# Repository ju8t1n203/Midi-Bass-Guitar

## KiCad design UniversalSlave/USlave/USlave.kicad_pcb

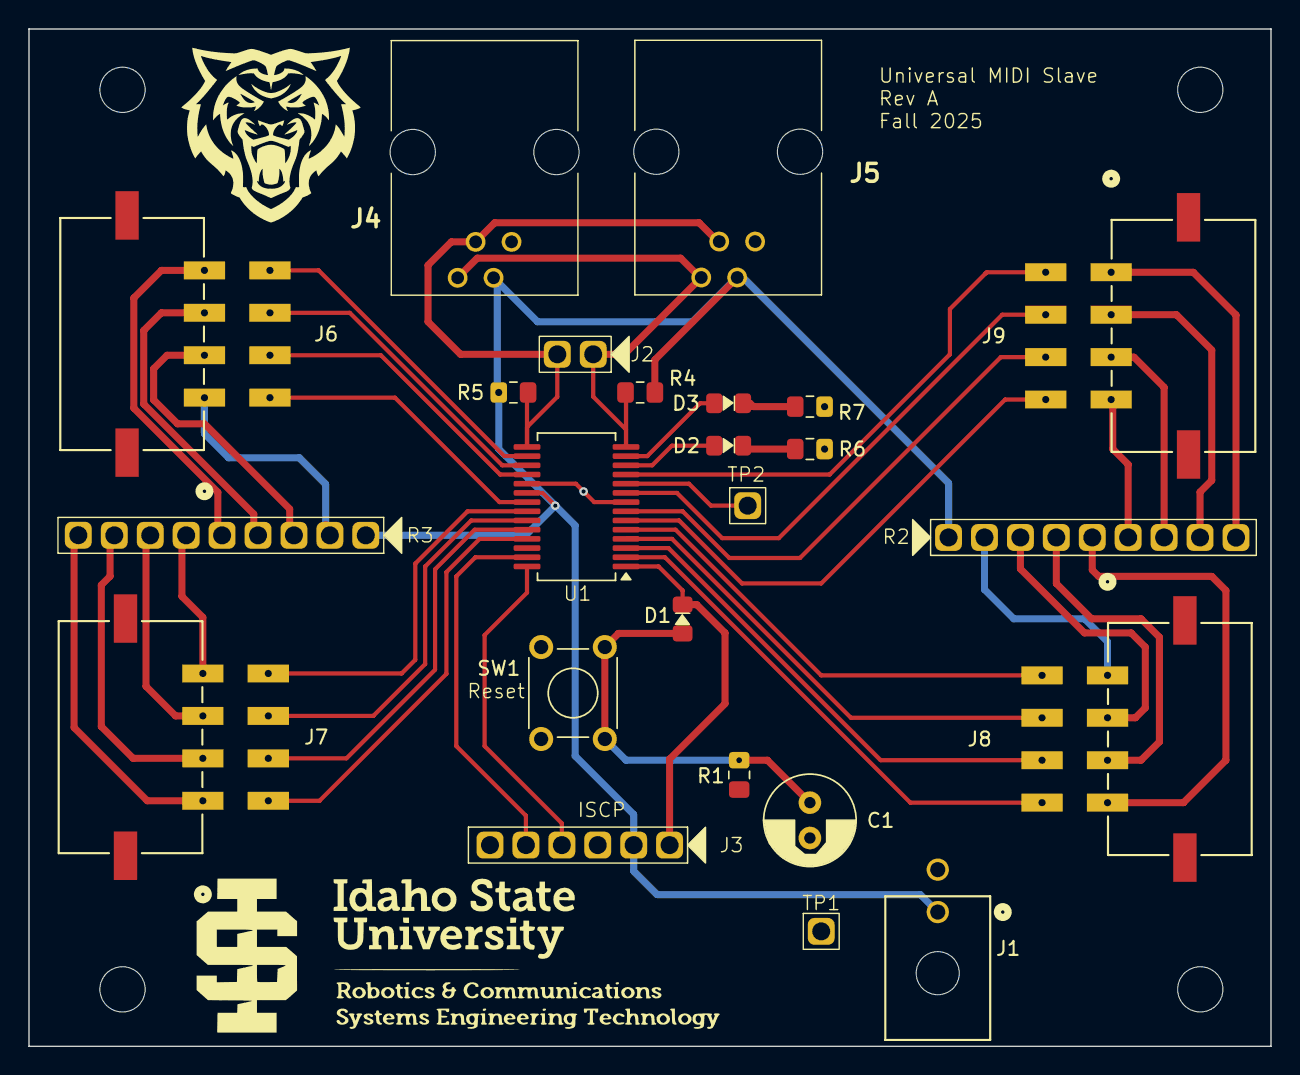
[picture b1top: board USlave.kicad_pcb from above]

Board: 2 copper layers, 87.8 x 71.9 mm, 24 parts (0 on the bottom side), 45 nets.

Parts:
C1: 10µF; C_Radial_D6.3mm_H11.0mm_P2.50mm
D1: 1N4148; D_0805
D2: Powered; D_0805
D3: Status; D_0805
J1: Power In; 2PinMolex
J2: I2C Test Point; 1X2_100mil_Header
J3: ISCP; 1X6_100mil_Header
J4: I2C Through; RJ11
J5: I2C In; RJ11
J6: 0-3; 8PinMolex_3.00mmPitch
J7: 4-7; 8PinMolex_3.00mmPitch
J8: 8-11; 8PinMolex_3.00mmPitch
J9: 12-15; 8PinMolex_3.00mmPitch
R1: 10KΩ; C_0805
R2, R3: 330Ω; 1x9_100mil_Header
R4, R5: 2.2KΩ; C_0805
R6, R7: 330Ω; C_0805
SW1: Reset; SW_TH_Tactile_Omron_B3F-100x
TP1: GND; 1X1_100mil_Header
TP2: Clock Out; 1X1_100mil_Header
U1: PIC16F1788; SSOP-28_5.3x10.2mm_P0.65mm

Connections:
GND: C1.2, J1.2, J3.3, J4.1, J5.1, R6.2, R7.2, SW1.1, TP1.1, U1.8 (V_{SS}), U1.19 (V_{SS})
unnamed: C1.1, D1.2 (A), R1.2, SW1.2
unnamed: D1.1 (K), J3.1, U1.1 (RE3/~MCLR/V_{PP})
unnamed: D2.2 (A), U1.12 (RC1)
unnamed: D2.1 (K), R6.1
unnamed: D3.2 (A), U1.13 (RC2)
unnamed: D3.1 (K), R7.1
unnamed: J8.1, R2.2 (R1)
unnamed: J8.2, R2.3 (R2)
unnamed: J8.3, R2.4 (R3)
unnamed: J8.4, R2.5 (R4)
unnamed: J9.4, R2.6 (R5)
unnamed: J9.3, R2.7 (R6)
unnamed: J9.2, R2.8 (R7)
unnamed: J9.1, R2.9 (R8)
unnamed: J6.1, R3.2 (R1)
unnamed: J6.2, R3.3 (R2)
unnamed: J6.3, R3.4 (R3)
unnamed: J6.4, R3.5 (R4)
unnamed: J7.4, R3.6 (R5)
unnamed: J7.3, R3.7 (R6)
unnamed: J7.2, R3.8 (R7)
unnamed: J7.1, R3.9 (R8)
unnamed: J3.5, U1.27 (ICSPCLK/RB6)
unnamed: J3.4, U1.28 (ICSPDAT/RB7)
unnamed: J8.8, U1.2 (RA0)
unnamed: J8.7, U1.3 (RA1)
unnamed: J8.6, U1.4 (RA2)
unnamed: J8.5, U1.5 (RA3)
unnamed: J9.8, U1.6 (RA4)
unnamed: J9.7, U1.7 (RA5)
unnamed: TP2.1, U1.10 (RA6)
unnamed: J9.6, U1.9 (RA7)
unnamed: J6.5, U1.21 (RB0)
unnamed: J7.8, U1.22 (RB1)
unnamed: J7.7, U1.23 (RB2)
unnamed: J7.6, U1.24 (RB3)
unnamed: J7.5, U1.25 (RB4)
unnamed: J9.5, U1.11 (RC0)
unnamed: J2.1, J4.4, J5.4, R4.2, U1.14 (RC3)
unnamed: J2.2, J4.3, J5.3, R5.2, U1.15 (RC4)
unnamed: J6.8, U1.16 (RC5)
unnamed: J6.7, U1.17 (RC6)
unnamed: J6.6, U1.18 (RC7)
unnamed: J1.1, J3.2, J4.2, J5.2, R2.1 (COM), R3.1 (COM), R4.1, R5.1, U1.20 (V_{DD})

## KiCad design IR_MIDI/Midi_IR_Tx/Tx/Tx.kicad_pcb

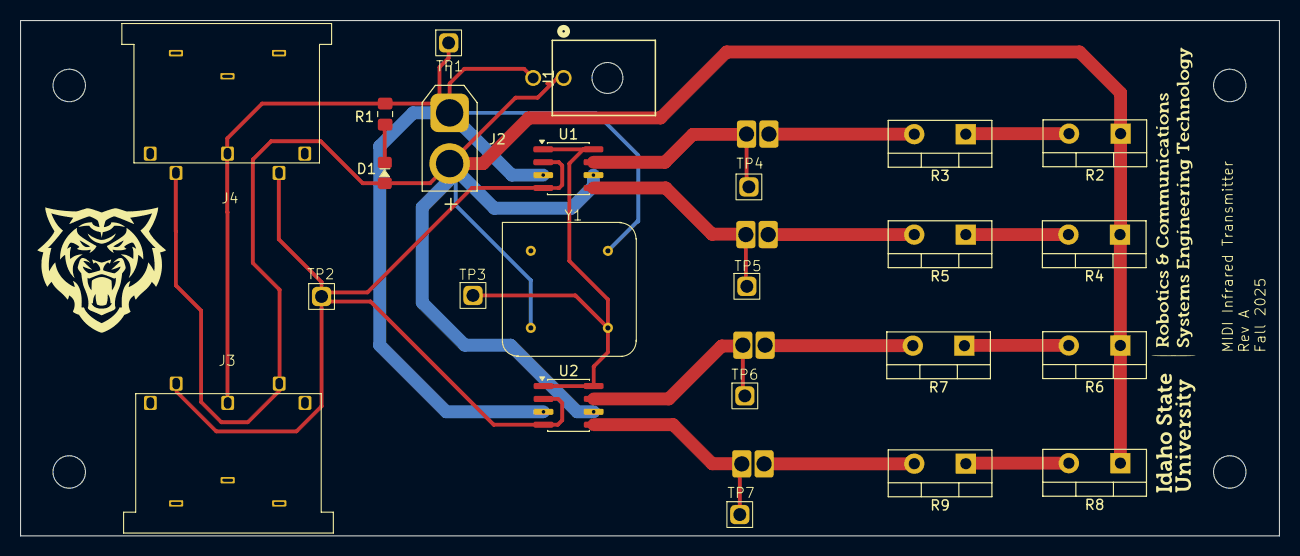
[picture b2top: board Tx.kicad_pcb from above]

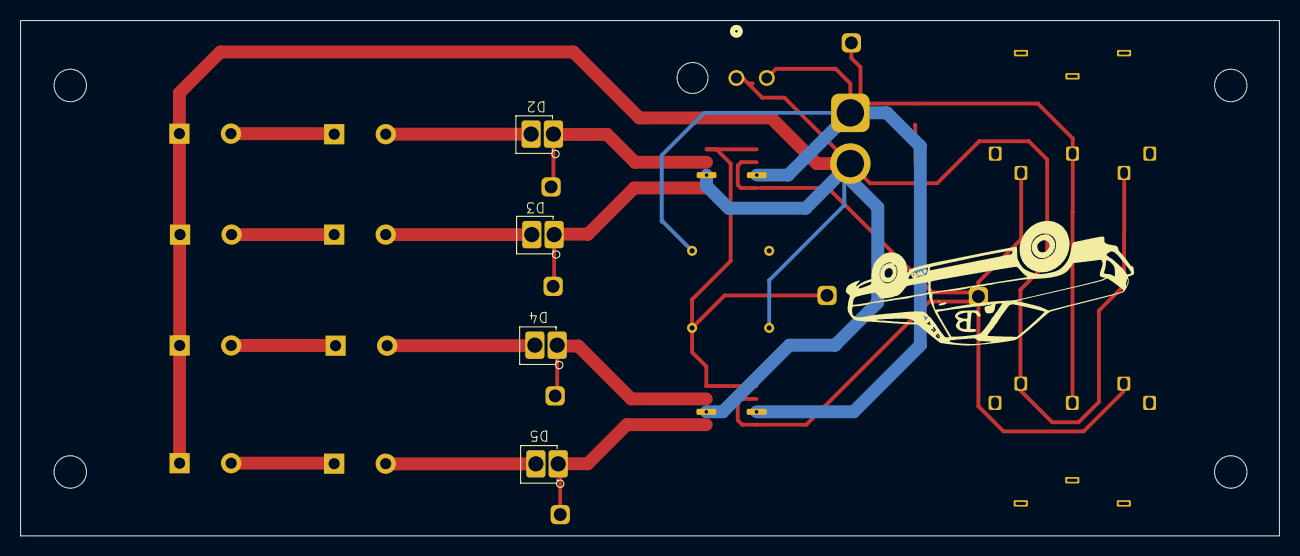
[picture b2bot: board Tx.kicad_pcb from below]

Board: 2 copper layers, 124.1 x 50.8 mm, 28 parts (4 on the bottom side), 17 nets.

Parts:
D1: LED_Filled; D_0805
D2, D3, D4, D5: D_Filled; Fat_2Pin_D
J1: FanPower; 2PinMolex
J2: Power In; AMASS_XT30U-F_1x02_P5.0mm_Vertical
J3: MIDI Thr; DIN-5PIN_MIDI
J4: MIDI in; DIN-5PIN_MIDI
R1: 330Ω; C_0805
R2, R3, R4, R5, R6, R7, R8, R9: 2Ω; TO-220-2_Vertical
TP1: GND; 1X1_100mil_Header
TP2: MIDI_Input; 1X1_100mil_Header
TP3: 1MHzTP; 1X1_100mil_Header
TP4: IR1; 1X1_100mil_Header
TP5: IR2; 1X1_100mil_Header
TP6: IR3; 1X1_100mil_Header
TP7: IR4; 1X1_100mil_Header
U1, U2: MCP14E3; SOIC-8_3.9x4.9mm_P1.27mm
Y1: 1MHz; 300x300Mil_4Pin_Y

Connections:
GND: J1.2, J2.1, J3.2, J4.2, R1.2, TP1.1, U1.3 (GND), U2.3 (GND), Y1.4
unnamed: D1.1 (K), R1.1
unnamed: D2.1 (A), R3.2
unnamed: D2.2 (K), TP4.1, U1.7 (~OUTA)
unnamed: D3.1 (A), R5.2
unnamed: D3.2 (K), TP5.1, U1.5 (~OUTB)
unnamed: D4.1 (A), R7.2
unnamed: D4.2 (K), TP6.1, U2.7 (~OUTA)
unnamed: D5.1 (A), R9.2
unnamed: D5.2 (K), TP7.1, U2.5 (~OUTB)
unnamed: R2.2, R3.1
unnamed: R4.2, R5.1
unnamed: R6.2, R7.1
unnamed: R8.2, R9.1
unnamed: TP3.1, U1.1 (ENA), U1.8 (ENB), U2.1 (ENA), U2.8 (ENB), Y1.5
unnamed: J3.5, J4.5, TP2.1, U1.2 (INA), U1.4 (INB), U2.2 (INA), U2.4 (INB)
unnamed: D1.2 (A), J1.1, J2.2, J3.4, J4.4, R2.1, R4.1, R6.1, R8.1, U1.6 (VCC), U2.6 (VCC), Y1.8

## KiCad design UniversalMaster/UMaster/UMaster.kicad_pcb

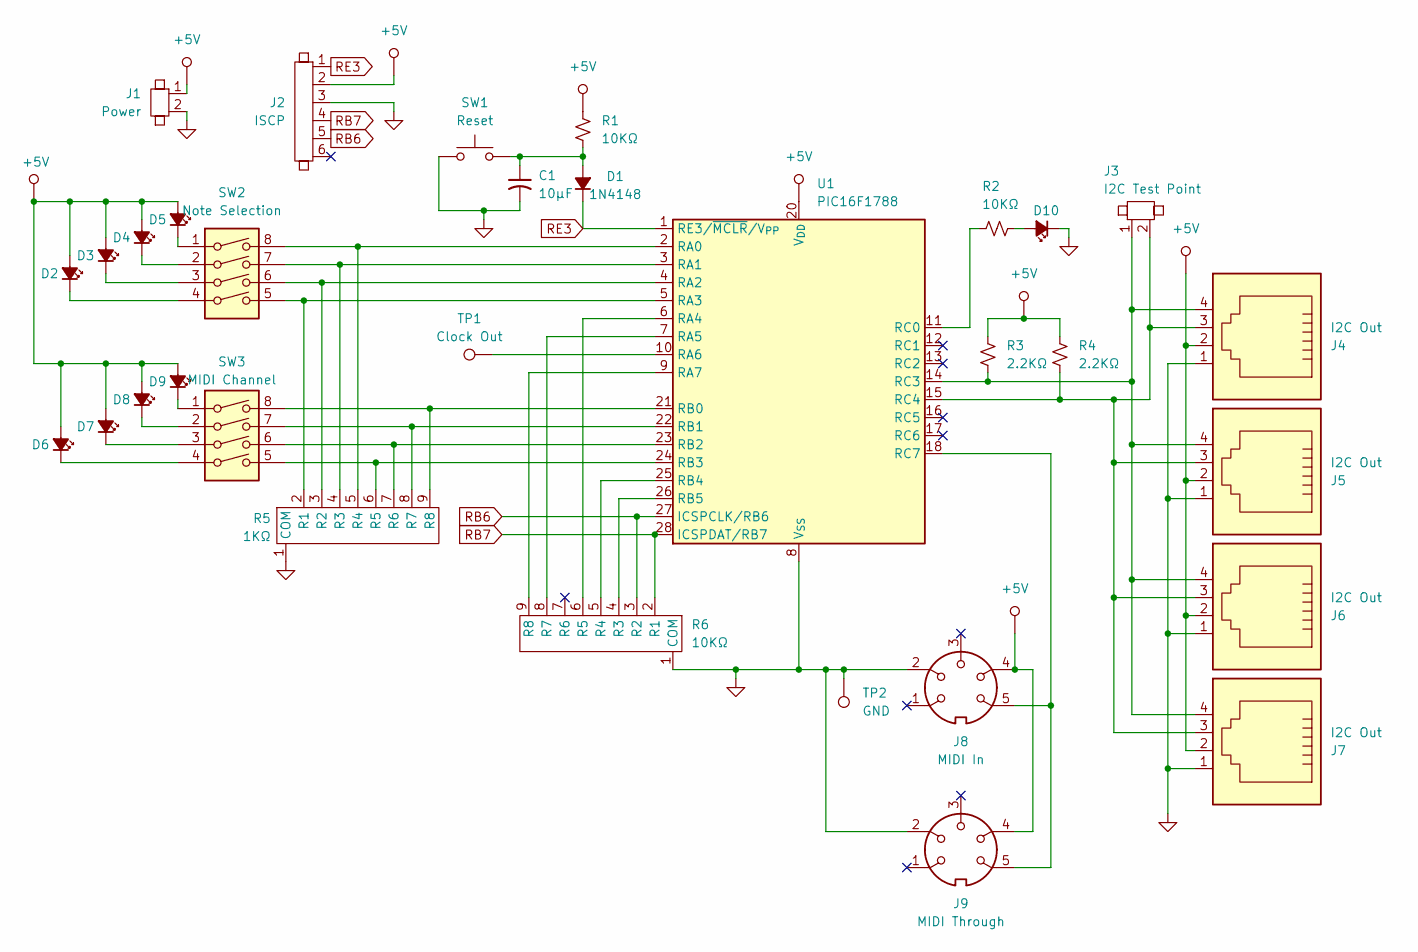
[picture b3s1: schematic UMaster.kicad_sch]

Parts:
C1: 10µF; C_Radial_D6.3mm_H11.0mm_P2.50mm
D1: 1N4148; D_0805
D2, D3, D4, D5, D6, D7, D8, D9, D10: LED_Small_Filled; D_0805
J1: Power; 2PinMolex
J2: ISCP; 1X6_100mil_Header
J3: I2C Test Point; 1X2_100mil_Header
J4, J5, J6, J7: I2C Out; RJ11
J8: MIDI In; DIN-5PIN_MIDI
J9: MIDI Through; DIN-5PIN_MIDI
R1, R2: 10KΩ; C_0805
R3, R4: 2.2KΩ; C_0805
R5: 1KΩ; 1x9_100mil_Header
R6: 10KΩ; 1x9_100mil_Header
SW1: Reset; SW_PUSH_6mm
SW2: Note Selection; DIP-8_W7.62mm
SW3: MIDI Channel; DIP-8_W7.62mm
TP1: Clock Out; 1X1_100mil_Header
TP2: GND; 1X1_100mil_Header
U1: PIC16F1788; QFN-28-1EP_6x6mm_P0.65mm_EP4.25x4.25mm

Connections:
GND: C1.2, D10.1 (K), J1.2, J2.3, J4.1, J5.1, J6.1, J7.1, J8.2, J9.2, R5.1 (COM), R6.1 (COM), SW1.1, TP2.1, U1.8 (V_{SS}), U1.19 (V_{SS})
unnamed: C1.1, D1.2 (A), R1.2, SW1.2
unnamed: D2.1 (K), SW2.4
unnamed: D3.1 (K), SW2.3
unnamed: D4.1 (K), SW2.2
unnamed: D5.1 (K), SW2.1
unnamed: D6.1 (K), SW3.4
unnamed: D7.1 (K), SW3.3
unnamed: D8.1 (K), SW3.2
unnamed: D9.1 (K), SW3.1
unnamed: D10.2 (A), R2.2
unnamed: R5.2 (R1), SW2.5, U1.5 (RA3)
unnamed: R5.3 (R2), SW2.6, U1.4 (RA2)
unnamed: R5.4 (R3), SW2.7, U1.3 (RA1)
unnamed: R5.5 (R4), SW2.8, U1.2 (RA0)
unnamed: R5.6 (R5), SW3.5, U1.24 (RB3)
unnamed: R5.7 (R6), SW3.6, U1.23 (RB2)
unnamed: R5.8 (R7), SW3.7, U1.22 (RB1)
unnamed: R5.9 (R8), SW3.8, U1.21 (RB0)
unnamed: R6.4 (R3), U1.26 (RB5)
unnamed: R6.5 (R4), U1.25 (RB4)
unnamed: R6.6 (R5), U1.6 (RA4)
unnamed: R6.8 (R7), U1.7 (RA5)
unnamed: R6.9 (R8), U1.9 (RA7)
unnamed: TP1.1, U1.10 (RA6)
unnamed: R2.1, U1.11 (RC0)
unnamed: J3.1, J4.4, J5.4, J6.4, J7.4, R3.2, U1.14 (RC3)
unnamed: J3.2, J4.3, J5.3, J6.3, J7.3, R4.2, U1.15 (RC4)
unnamed: J8.5, J9.5, U1.18 (RC7)
RB6: J2.5, R6.3 (R2), U1.27 (ICSPCLK/RB6)
RB7: J2.4, R6.2 (R1), U1.28 (ICSPDAT/RB7)
RE3: D1.1 (K), J2.1, U1.1 (RE3/~MCLR/V_{PP})

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
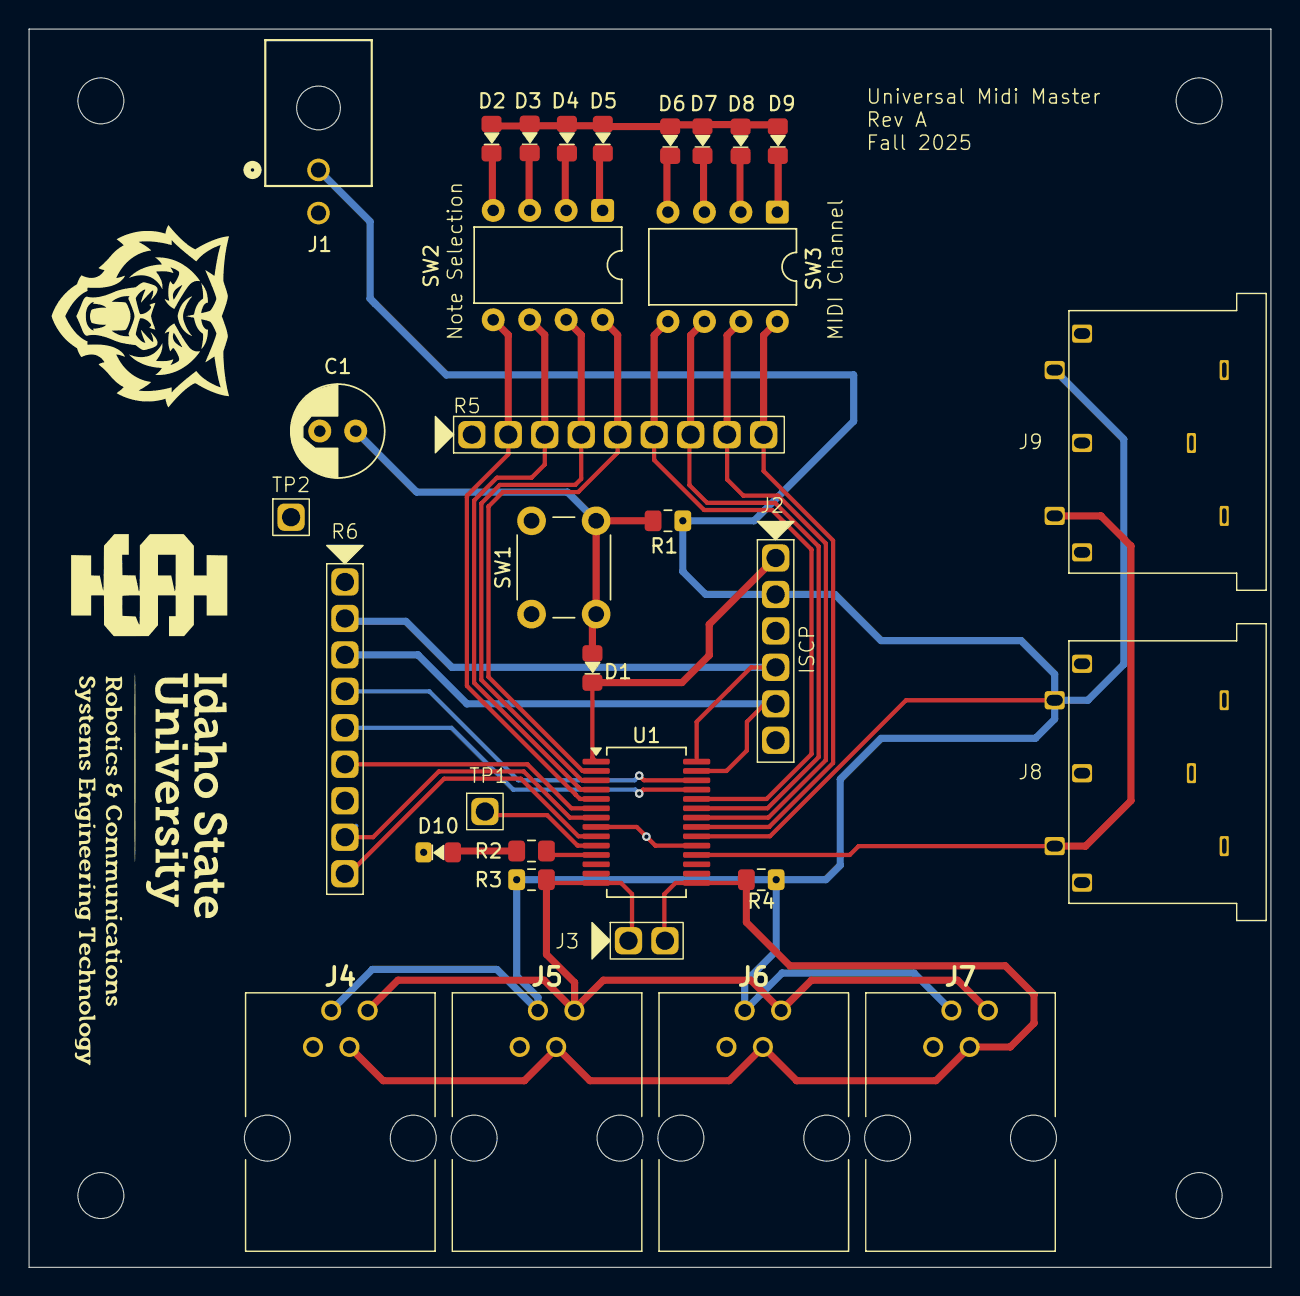
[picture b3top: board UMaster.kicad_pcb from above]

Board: 2 copper layers, 86.5 x 86.2 mm, 32 parts (0 on the bottom side), 34 nets.

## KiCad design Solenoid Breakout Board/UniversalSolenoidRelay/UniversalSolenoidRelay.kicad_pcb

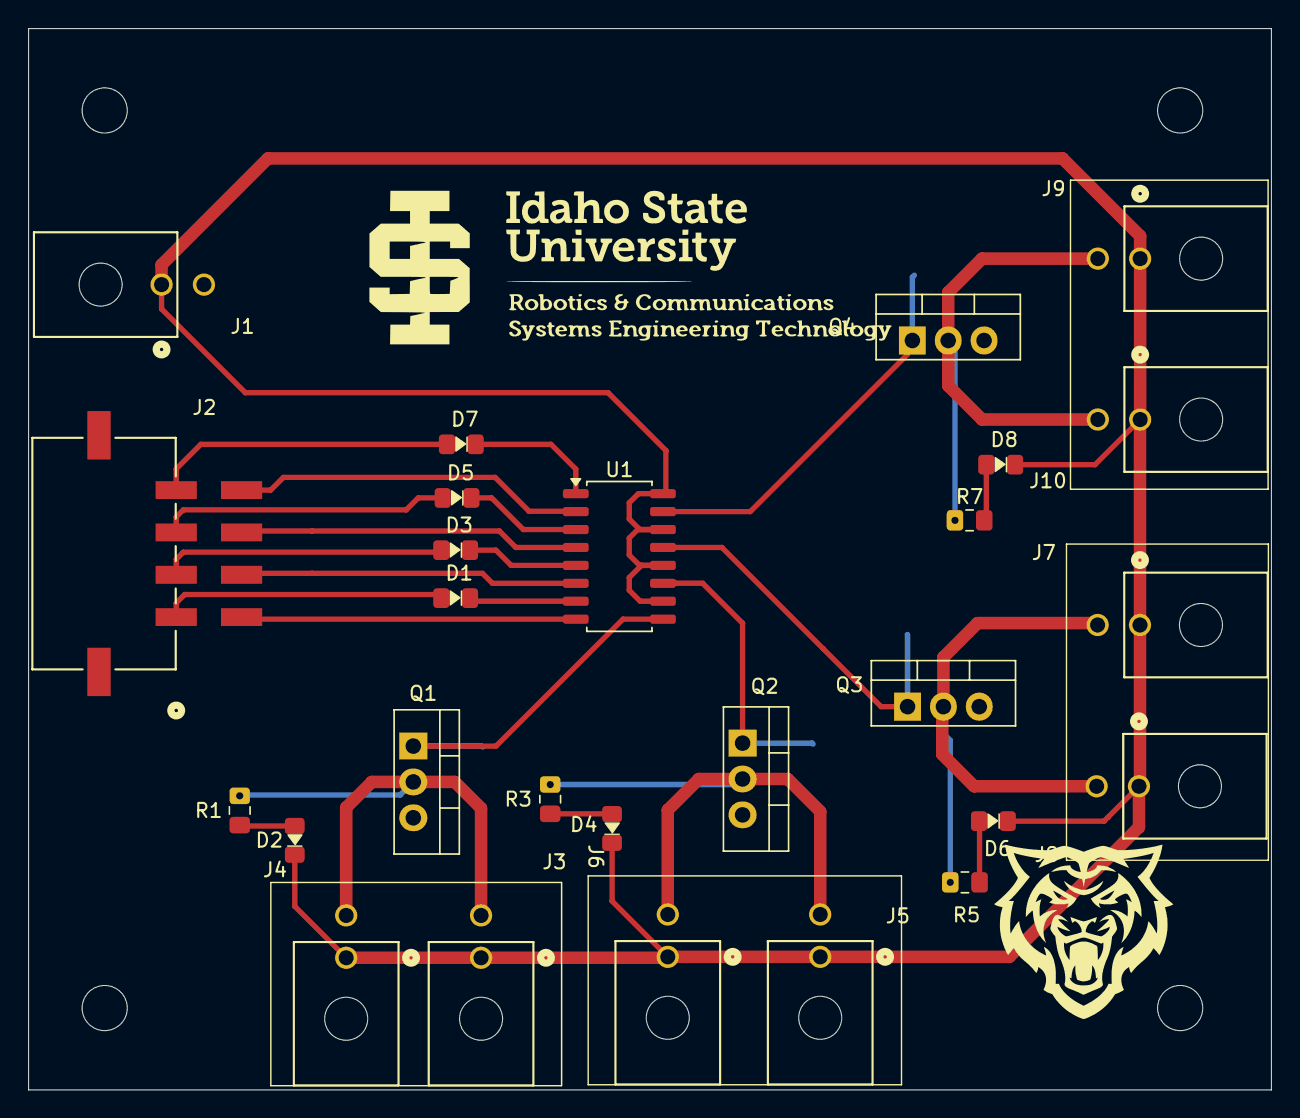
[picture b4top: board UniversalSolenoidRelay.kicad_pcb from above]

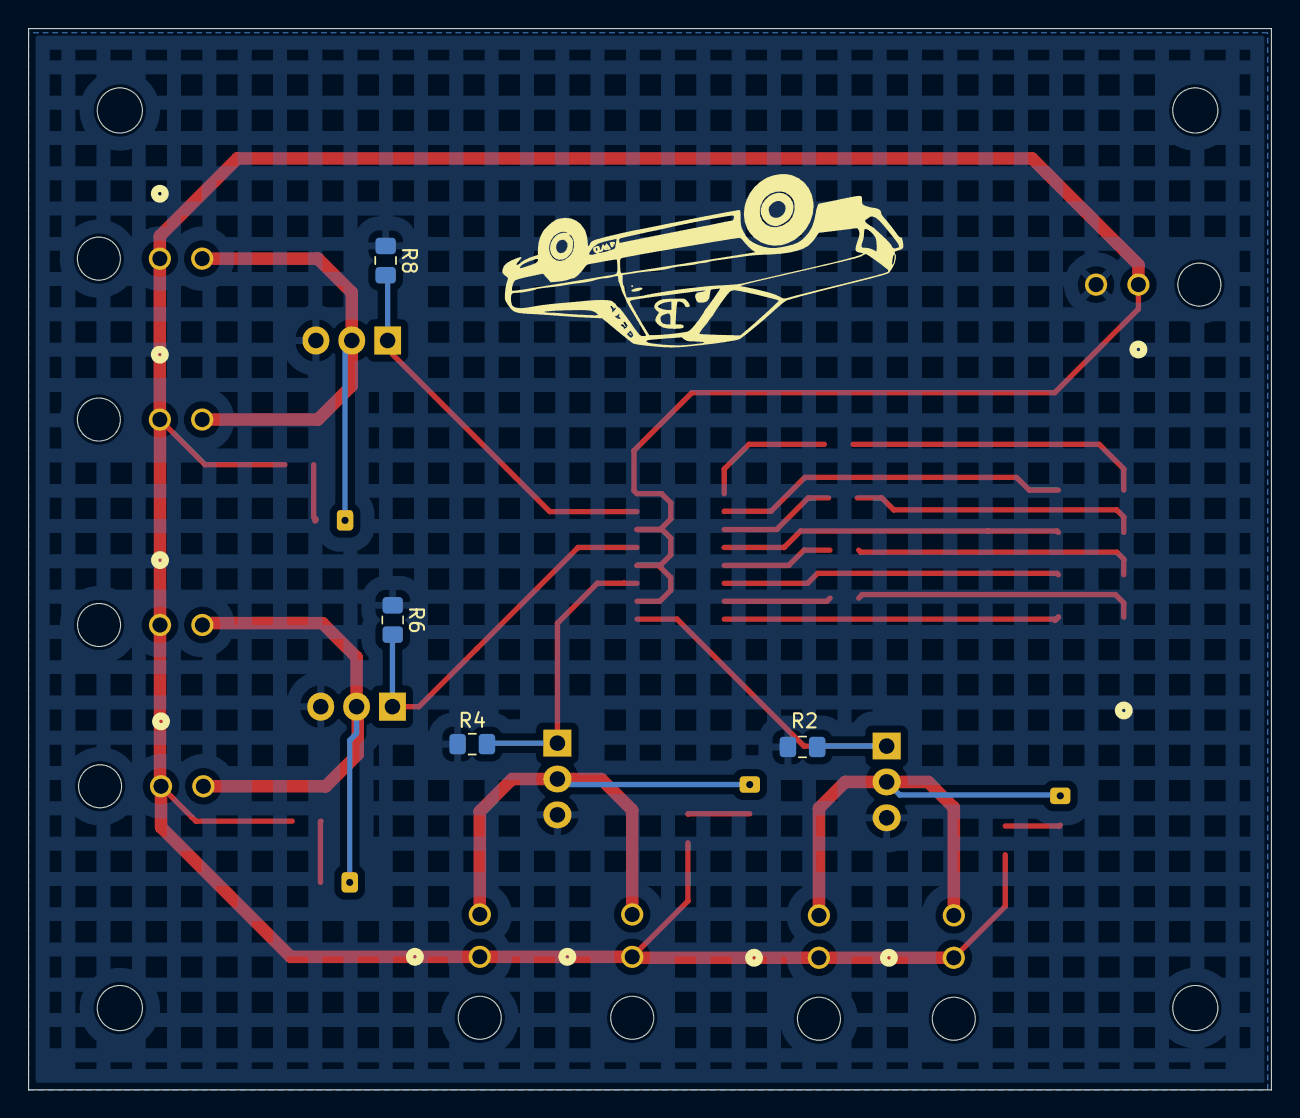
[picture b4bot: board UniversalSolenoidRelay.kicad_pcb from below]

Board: 2 copper layers, 88.1 x 75.2 mm, 31 parts (4 on the bottom side), 26 nets.

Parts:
D1, D3, D5, D7: LED; D_0805
D2, D4, D6, D8: 1N4148; D_0805
J1: Power In; 2PinMolex
J2: Signal In; 8PinMolex_3.00mmPitch
J3, J4, J5, J6, J7, J8, J9, J10: Solenoid; 2PinMolex
Q1, Q2, Q3, Q4: IRF540N; TO-220-3_Vertical
R1, R3, R5, R7: 1KΩ; C_0805
R2, R4, R6, R8: 1kΩ; C_0805
U1: LTV-247; SOP-16_4.4x10.4mm_P1.27mm

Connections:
GND: J1.2, Q1.3 (S), Q2.3 (S), Q3.3 (S), Q4.3 (S), R2.1, R4.1, R6.1, R8.1
unnamed: D1.2 (A), J2.1
unnamed: D1.1 (K), U1.7
unnamed: D2.2 (A), R1.2
unnamed: D3.2 (A), J2.2
unnamed: D3.1 (K), U1.5
unnamed: D4.2 (A), R3.2
unnamed: D5.2 (A), J2.3
unnamed: D5.1 (K), U1.3
unnamed: D6.2 (A), R5.2
unnamed: D7.2 (A), J2.4
unnamed: D7.1 (K), U1.1
unnamed: D8.2 (A), R7.2
unnamed: D2.1 (K), D4.1 (K), D6.1 (K), D8.1 (K), J1.1, J3.1, J4.1, J5.1, J6.1, J7.1, J8.1, J9.1, J10.1, U1.10, U1.12, U1.14, U1.16
unnamed: J2.5, U1.8
unnamed: J2.6, U1.6
unnamed: J2.7, U1.4
unnamed: J2.8, U1.2
unnamed: J3.2, J4.2, Q1.2 (D), R1.1
unnamed: Q1.1 (G), R2.2, U1.9
unnamed: J5.2, J6.2, Q2.2 (D), R3.1
unnamed: Q2.1 (G), R4.2, U1.11
unnamed: J7.2, J8.2, Q3.2 (D), R5.1
unnamed: Q3.1 (G), R6.2, U1.13
unnamed: J9.2, J10.2, Q4.2 (D), R7.1
unnamed: Q4.1 (G), R8.2, U1.15

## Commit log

2025-11-05 updated file structures and refreshed MIDI circuits
2025-11-05 started modeling new fret system
2025-11-11 some cad work and updated midi note charts
2025-11-11 sudo code uploaded
2025-11-12 added i2c protocol
2025-11-13 updated Universal Master schematic
2025-11-13 made new master, pluck and fret circuits
2025-11-14 decided on utilizing a universal setup for the slave board
2025-11-15 designed universal PCB
2025-11-16 revised IR Tx board
2025-11-16 made solenoid relay circuit and board
